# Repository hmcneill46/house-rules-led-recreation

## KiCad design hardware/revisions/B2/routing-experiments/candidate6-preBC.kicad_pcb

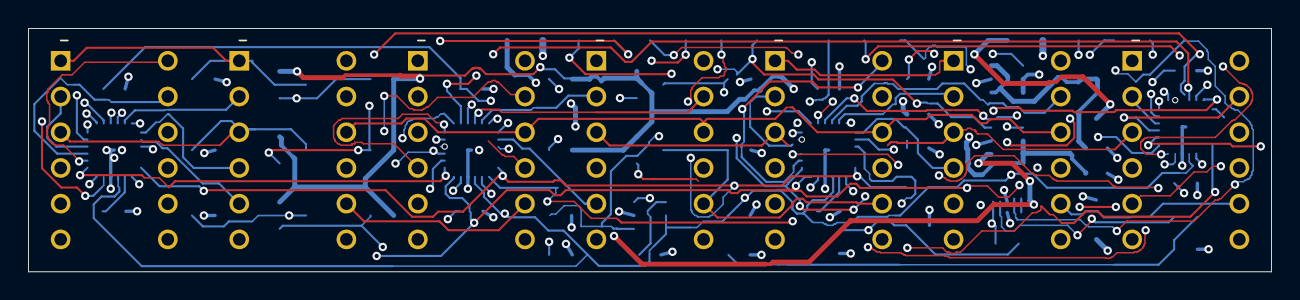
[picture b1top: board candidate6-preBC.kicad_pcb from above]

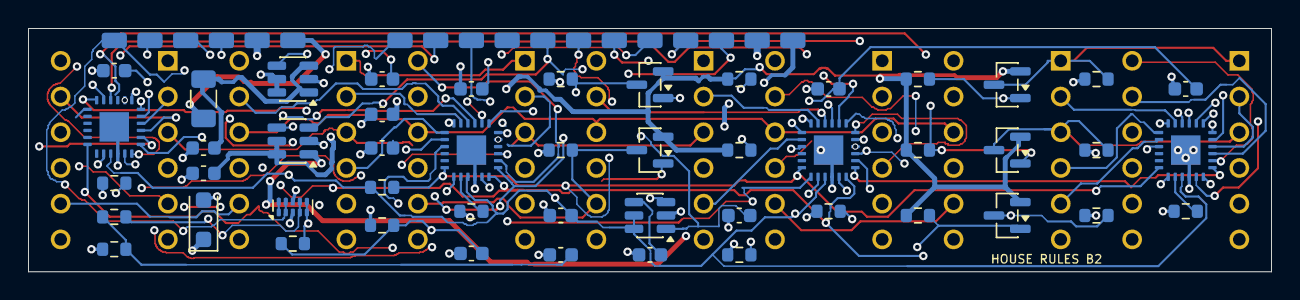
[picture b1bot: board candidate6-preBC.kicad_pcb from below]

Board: 6 copper layers, 88.4 x 17.3 mm, 74 parts (67 on the bottom side), 87 nets.

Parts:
C1, C2, C3, C4: 100n 50V X7R; C_0603_1608Metric
C5, C6, C7, C14: 1u 16V X7R; C_0603_1608Metric
C8: 4u7 16V X5R; C_0603_1608Metric
C9, C10, C13: 1n 50V X7R; C_0603_1608Metric
C11, C12: 10n 50V X7R; C_0603_1608Metric
D1: SMF5.0A; D_SOD-123F
DS1, DS2, DS3, DS4, DS5, DS6, DS7: LMD07057AUE-101B
F1: 750mA PPTC; Fuse_1206_3216Metric
J1: +5V; WirePad_B2
J2, J14: GND; WirePad_B2
J3: +3V3; WirePad_B2
J4: SIN; WirePad_B2
J5: SCLK; WirePad_B2
J6: LAT; WirePad_B2
J7: BLANK; WirePad_B2
J8: DRIVER_EN; WirePad_B2
J9: CC1_ADC; WirePad_B2
J10: CC2_ADC; WirePad_B2
J11, J17: USB_DM; WirePad_B2
J12, J18: USB_DP; WirePad_B2
J13: VBUS; WirePad_B2
J15: CC1; WirePad_B2
J16: CC2; WirePad_B2
Q1, Q2, Q3, Q4, Q5: AO3401A; SOT-23
R1, R2, R3, R4: 6k98 1%; R_0603_1608Metric
R5, R6, R7, R8, R9, R15: 4k7 1%; R_0603_1608Metric
R10, R11, R12, R13, R14: 10k 1%; R_0603_1608Metric
R16: 100k 1%; R_0603_1608Metric
R17, R18, R19, R20: 47k 1%; R_0603_1608Metric
U1, U2, U3, U4: TLC59282RGER; RGE0024C
U5, U6, U8: TPS22918DBVR; SOT-23-6
U7: TPD4E05U06DQAR; USON-10_2.5x1.0mm_P0.5mm

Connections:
+3V3: C5.1, J3.1, U5.1
+5V: C6.1, J1.1, U6.1, U8.5, U8.6
BLANK: J7.1, R15.1, U1.18, U2.18, U3.18, U4.18
CC1: J15.1, R17.1, U7.4, U7.7
CC1_ADC: C11.1, J9.1, R17.2, R18.1
CC2: J16.1, R19.1, U7.5, U7.6
CC2_ADC: C12.1, J10.1, R19.2, R20.1
COL1_A: DS1.1, DS2.1, DS3.1, DS4.1, DS5.1, DS6.1, DS7.1, Q1.3, R10.1
COL1_GATE: Q1.1, R5.1, U4.9
COL2_A: DS1.3, DS2.3, DS3.3, DS4.3, DS5.3, DS6.3, DS7.3, Q2.3, R11.1
COL2_GATE: Q2.1, R6.1, U4.10
COL3_A: DS1.10, DS2.10, DS3.10, DS4.10, DS5.10, DS6.10, DS7.10, Q3.3, R12.1
COL3_GATE: Q3.1, R7.1, U4.11
COL4_A: DS1.7, DS2.7, DS3.7, DS4.7, DS5.7, DS6.7, DS7.7, Q4.3, R13.1
COL4_GATE: Q4.1, R8.1, U4.12
COL5_A: DS1.8, DS2.8, DS3.8, DS4.8, DS5.8, DS6.8, DS7.8, Q5.3, R14.1
COL5_GATE: Q5.1, R9.1, U4.13
CT_3V3: C9.1, U5.4
CT_5V: C10.1, U6.4
CT_INPUT: C13.1, U8.4
D1_ROW1_K: DS1.12, U1.2
D1_ROW2_K: DS1.11, U1.3
D1_ROW3_K: DS1.2, U1.4
D1_ROW4_K: DS1.9, U1.5
D1_ROW5_K: DS1.4, U1.6
D1_ROW6_K: DS1.5, U1.7
D1_ROW7_K: DS1.6, U1.8
D1_ROW8_K: DS2.12, U1.9
D1_ROW9_K: DS2.11, U1.10
D1_ROW10_K: DS2.2, U1.11
D1_ROW11_K: DS2.9, U1.12
D1_ROW12_K: DS2.4, U1.13
D1_ROW13_K: DS2.5, U1.14
D1_ROW14_K: DS2.6, U1.15
D2_ROW1_K: DS3.12, U2.2
D2_ROW2_K: DS3.11, U2.3
D2_ROW3_K: DS3.2, U2.4
D2_ROW4_K: DS3.9, U2.5
D2_ROW5_K: DS3.4, U2.6
D2_ROW6_K: DS3.5, U2.7
D2_ROW7_K: DS3.6, U2.8
D2_ROW8_K: DS4.12, U2.9
D2_ROW9_K: DS4.11, U2.10
D2_ROW10_K: DS4.2, U2.11
D2_ROW11_K: DS4.9, U2.12
D2_ROW12_K: DS4.4, U2.13
D2_ROW13_K: DS4.5, U2.14
D2_ROW14_K: DS4.6, U2.15
D3_ROW1_K: DS5.12, U3.2
D3_ROW2_K: DS5.11, U3.3
D3_ROW3_K: DS5.2, U3.4
D3_ROW4_K: DS5.9, U3.5
D3_ROW5_K: DS5.4, U3.6
D3_ROW6_K: DS5.5, U3.7
D3_ROW7_K: DS5.6, U3.8
D3_ROW8_K: DS6.12, U3.9
D3_ROW9_K: DS6.11, U3.10
D3_ROW10_K: DS6.2, U3.11
D3_ROW11_K: DS6.9, U3.12
D3_ROW12_K: DS6.4, U3.13
D3_ROW13_K: DS6.5, U3.14
D3_ROW14_K: DS6.6, U3.15
D4_ROW1_K: DS7.12, U4.2
D4_ROW2_K: DS7.11, U4.3
D4_ROW3_K: DS7.2, U4.4
D4_ROW4_K: DS7.9, U4.5
D4_ROW5_K: DS7.4, U4.6
D4_ROW6_K: DS7.5, U4.7
D4_ROW7_K: DS7.6, U4.8
DRIVER_EN: J8.1, R16.1, U5.3, U6.3
FUSED_VBUS: C14.1, F1.2, U8.1, U8.3
GND: C1.2, C2.2, C3.2, C4.2, C5.2, C6.2, C7.2, C8.2, C9.2, C10.2, C11.2, C12.2, C13.2, C14.2, D1.2, J2.1, J14.1, R1.2, R2.2, R3.2, R4.2, R10.2, R11.2, R12.2, R13.2, R14.2, R16.2, R18.2, R20.2, U1.22, U1.25, U2.22, U2.25, U3.22, U3.25, U4.22, U4.25, U5.2, U6.2, U7.3, U7.8, U8.2
IREF1: R1.1, U1.20
IREF2: R2.1, U2.20
IREF3: R3.1, U3.20
IREF4: R4.1, U4.20
LAT: J6.1, U1.1, U2.1, U3.1, U4.1
SCLK: J5.1, U1.24, U2.24, U3.24, U4.24
SERIAL_1_2: U1.19, U2.23
SERIAL_2_3: U2.19, U3.23
SERIAL_3_4: U3.19, U4.23
SIN: J4.1, U1.23
SW_3V3: C1.1, C2.1, C3.1, C4.1, C7.1, R15.2, U1.21, U2.21, U3.21, U4.21, U5.5, U5.6
USB_DM: J11.1, J17.1, U7.1, U7.10
USB_DP: J12.1, J18.1, U7.2, U7.9
VBUS: D1.1, F1.1, J13.1
VLED_5V: C8.1, Q1.2, Q2.2, Q3.2, Q4.2, Q5.2, R5.2, R6.2, R7.2, R8.2, R9.2, U6.5, U6.6
